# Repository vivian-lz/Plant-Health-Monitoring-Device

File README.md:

# Plant-Health-Monitoring-Device
This device tells the user when a plant needs water or sunlight based on light and soil moisture sensors and two LEDs.

All PCBs were designed in Eagle by myself, manufactured through JLCPCB, and soldered using a soldering iron for assembly to create the device.
Code was created utilizing the Arduino IDE.

Version 1: Utilizes sensor modules in order to create the device (complete). Version 1 will be tested utilizing a breadboard to ensure that the setup will work for further iterations.

Version 2: Utilizes raw ICs in order to create the device (in progress).

Version 3: Will include ML processing and a display to predict when the device will need water next (based on previous data).

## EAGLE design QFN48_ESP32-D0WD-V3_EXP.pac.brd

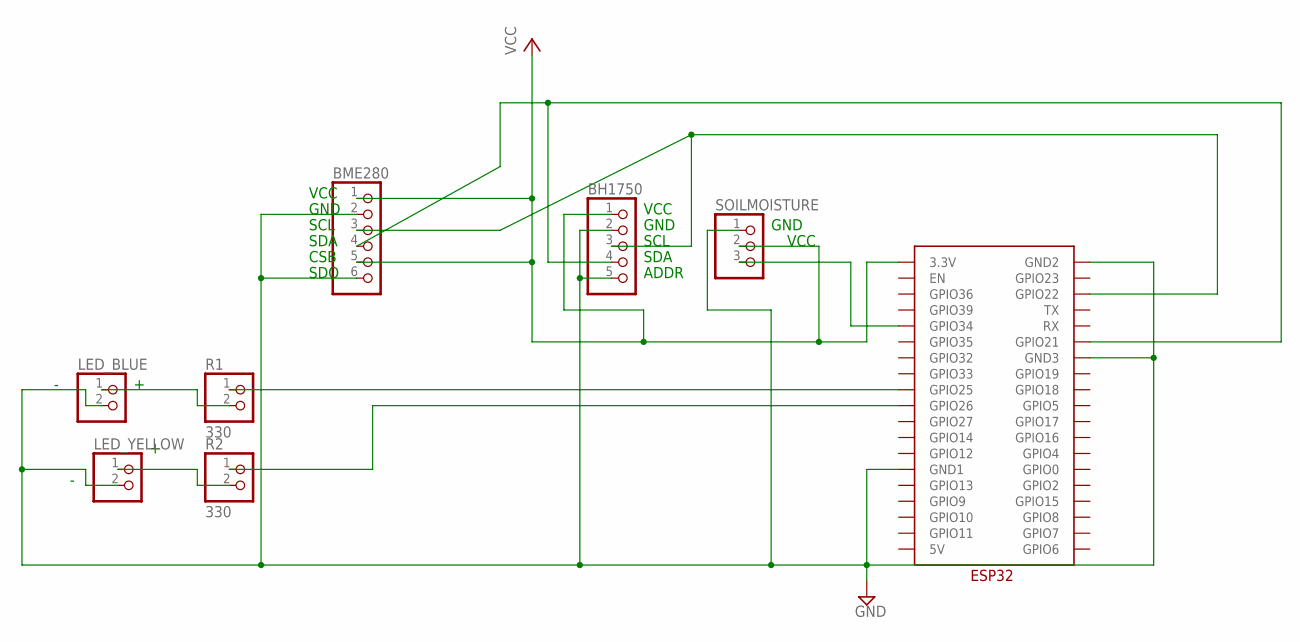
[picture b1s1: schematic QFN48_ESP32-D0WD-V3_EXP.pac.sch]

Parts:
BH1750: PINHD-1X5/90; 1X05/90
BME280: PINHD-1X6/90; 1X06/90
LED_BLUE: PINHD-1X2/90; 1X02/90
LED_YELLOW: PINHD-1X2/90; 1X02/90
R1, R2: 330; 1X02/90
SOILMOISTURE: PINHD-1X3/90; 1X03/90
U$1: ESP32

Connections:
3V3: BH1750.1, BME280.1, BME280.5, SOILMOISTURE.2, U$1.3.3V
GND: BH1750.2, BH1750.5, BME280.2, BME280.6, LED_BLUE.2, LED_YELLOW.2, SOILMOISTURE.1, U$1.GND1, U$1.GND2, U$1.GND3
unnamed: R1.1, U$1.GPIO25
unnamed: LED_BLUE.1, R1.2
unnamed: LED_YELLOW.1, R2.2
unnamed: R2.1, U$1.GPIO26
SCL: BH1750.3, BME280.3, U$1.GPIO22
SDA: BH1750.4, BME280.4, U$1.GPIO21
SOIL_SIG: SOILMOISTURE.3, U$1.GPIO34

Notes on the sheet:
GND
VCC
SDA
SCL
CSB
SDO
ADDR

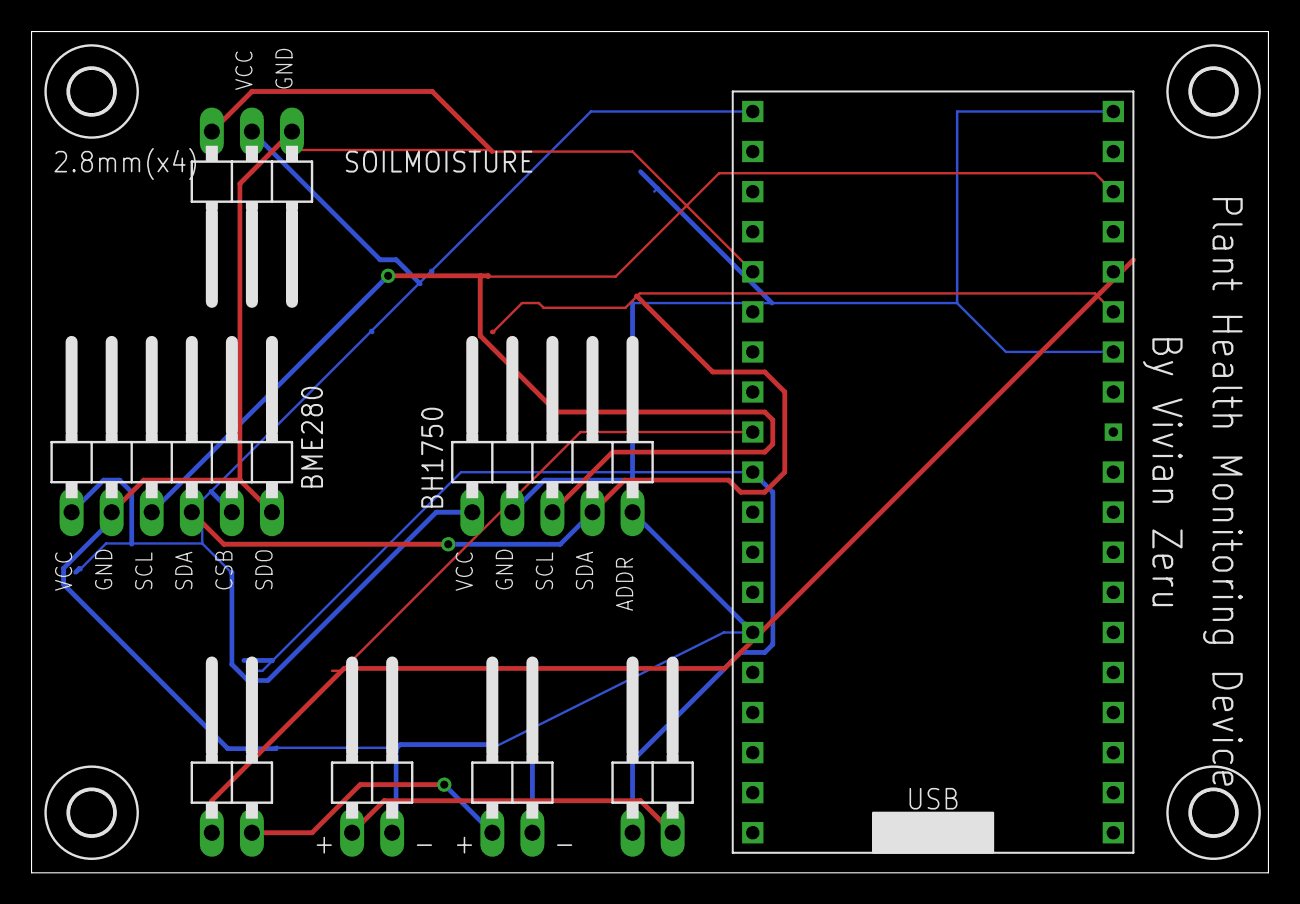
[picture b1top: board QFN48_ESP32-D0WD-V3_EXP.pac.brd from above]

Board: 2 copper layers, 78.4 x 53.3 mm, 12 parts (0 on the bottom side), 9 nets.

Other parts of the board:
U$2, U$3, U$4, U$5: 2,8

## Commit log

2025-06-14 Schematic and Layout Board for module edition (v1)
    This is the version of the device that utilizes modules for the sensors instead of raw ICs. The next iteration will utilize the raw ICs in the PCB design. This PCB was designed in Eagle. All the part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
2025-06-15 adding in firmware for esp32 module
    v1 of the general code for the firmware of this device (the module edition)
